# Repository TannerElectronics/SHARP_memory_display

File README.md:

# SHARP_memory_display
SPI breakout board example code for the Arduino platform

This example sketch is based on and requires two libraries from Adafruit. 

You will need to have installed the Adafruit GFX library from 
https://github.com/adafruit/Adafruit-GFX-Library 

As well as her SHARP library from 
https://github.com/adafruit/Adafruit_SHARP_Memory_Display

Images of front and back of module.

Click image below to follow link to YouTube demo.

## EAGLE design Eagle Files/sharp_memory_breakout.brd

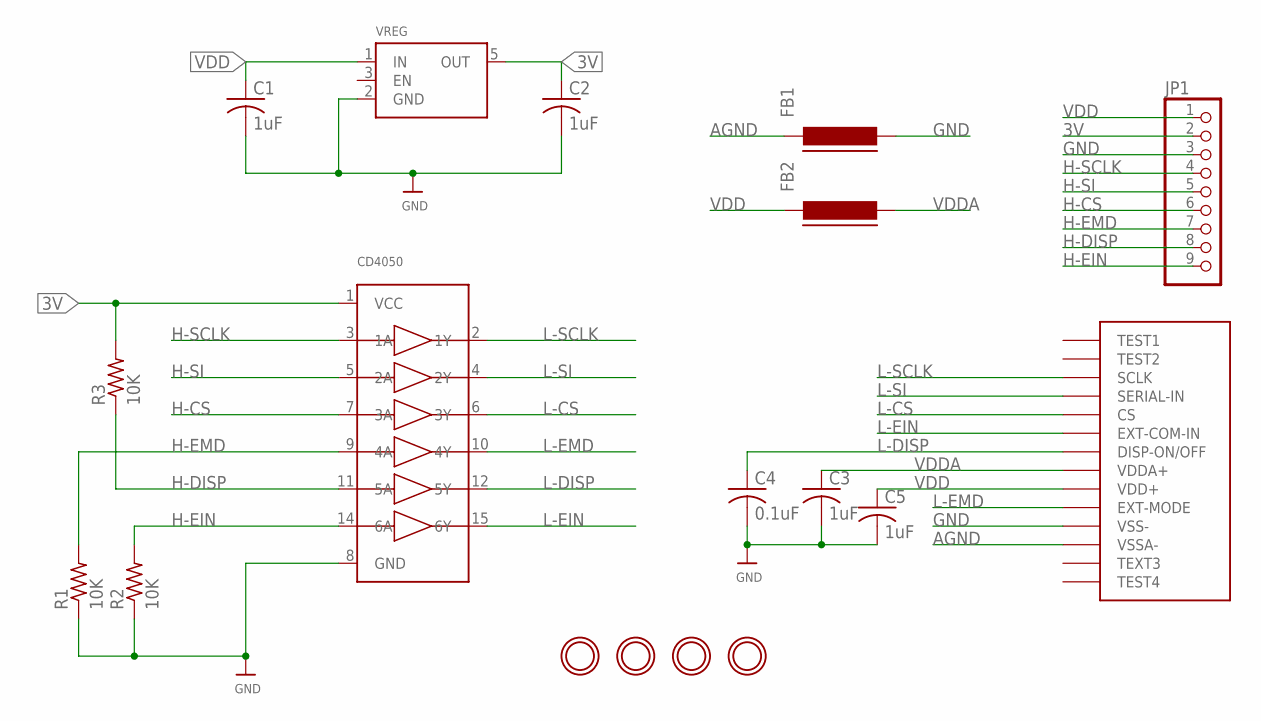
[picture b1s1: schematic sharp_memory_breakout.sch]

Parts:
C1, C2, C3, C5: 1uF; C0805K
C4: 0.1uF; C0805K
CD4050: 74HC4050D; SOIC16
FB1, FB2: FERRITE-0603; FB603
JP1: PINHD-1X9; 1X09-BIG
R1, R2, R3: 10K; R0805
U$1: SHARP-MEMORY
U$2, U$3, U$4, U$5: MOUNTINGHOLE3.0THIN; MOUNTINGHOLE_3.0_PLATEDTHIN
VREG: ADP121; SOT23-5

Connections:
3V: C2.1, CD4050.1 (VCC), JP1.2, R3.2, VREG.5 (OUT)
AGND: FB1.1, U$1.P$12 (VSSA-)
GND: C1.2, C2.2, C3.2, C4.2, C5.2, CD4050.8 (GND), FB1.2, JP1.3, R1.1, R2.1, U$1.P$11 (VSS-), VREG.2 (GND)
H-CS: CD4050.7 (3A), JP1.6
H-DISP: CD4050.11 (5A), JP1.8, R3.1
H-EIN: CD4050.14 (6A), JP1.9, R2.2
H-EMD: CD4050.9 (4A), JP1.7, R1.2
H-SCLK: CD4050.3 (1A), JP1.4
H-SI: CD4050.5 (2A), JP1.5
L-CS: CD4050.6 (3Y), U$1.P$5 (CS)
L-DISP: C4.1, CD4050.12 (5Y), U$1.P$7 (DISP-ON/OFF)
L-EIN: CD4050.15 (6Y), U$1.P$6 (EXT-COM-IN)
L-EMD: CD4050.10 (4Y), U$1.P$10 (EXT-MODE)
L-SCLK: CD4050.2 (1Y), U$1.P$3 (SCLK)
L-SI: CD4050.4 (2Y), U$1.P$4 (SERIAL-IN)
VDD: C1.1, C5.1, FB2.1, JP1.1, U$1.P$9 (VDD+), VREG.1 (IN)
VDDA: C3.1, FB2.2, U$1.P$8 (VDDA+)

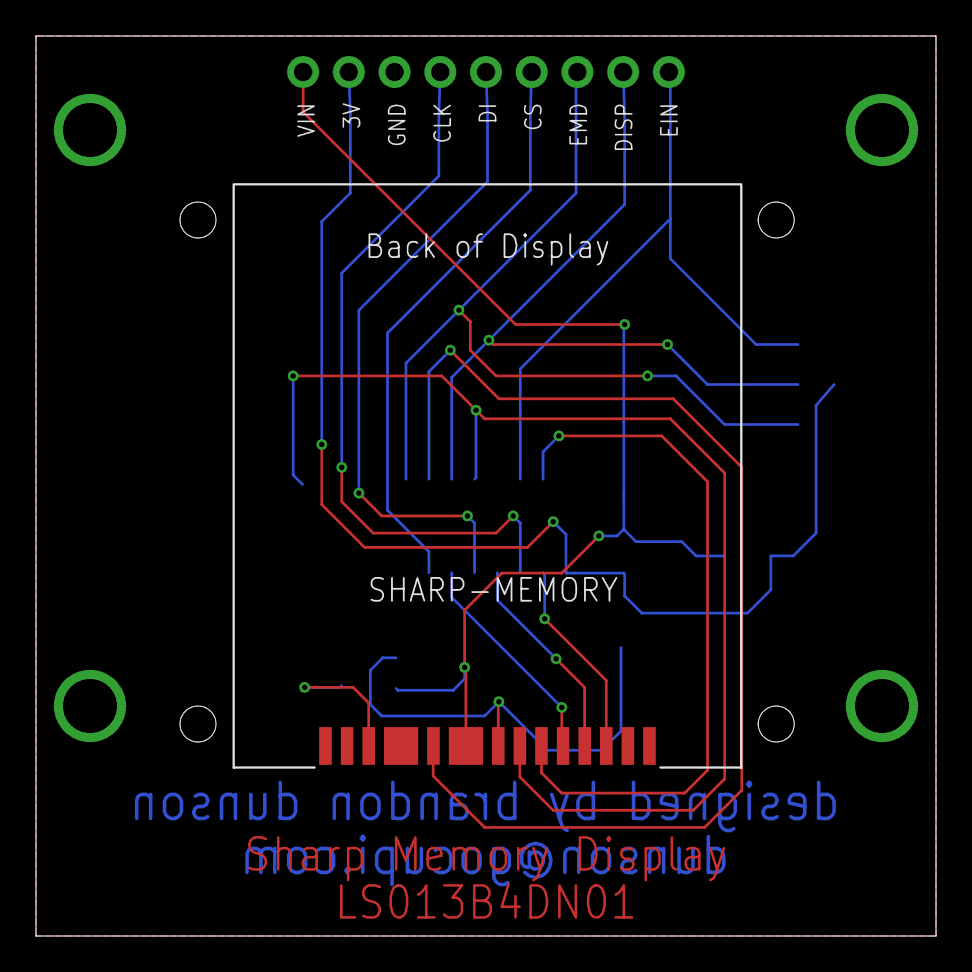
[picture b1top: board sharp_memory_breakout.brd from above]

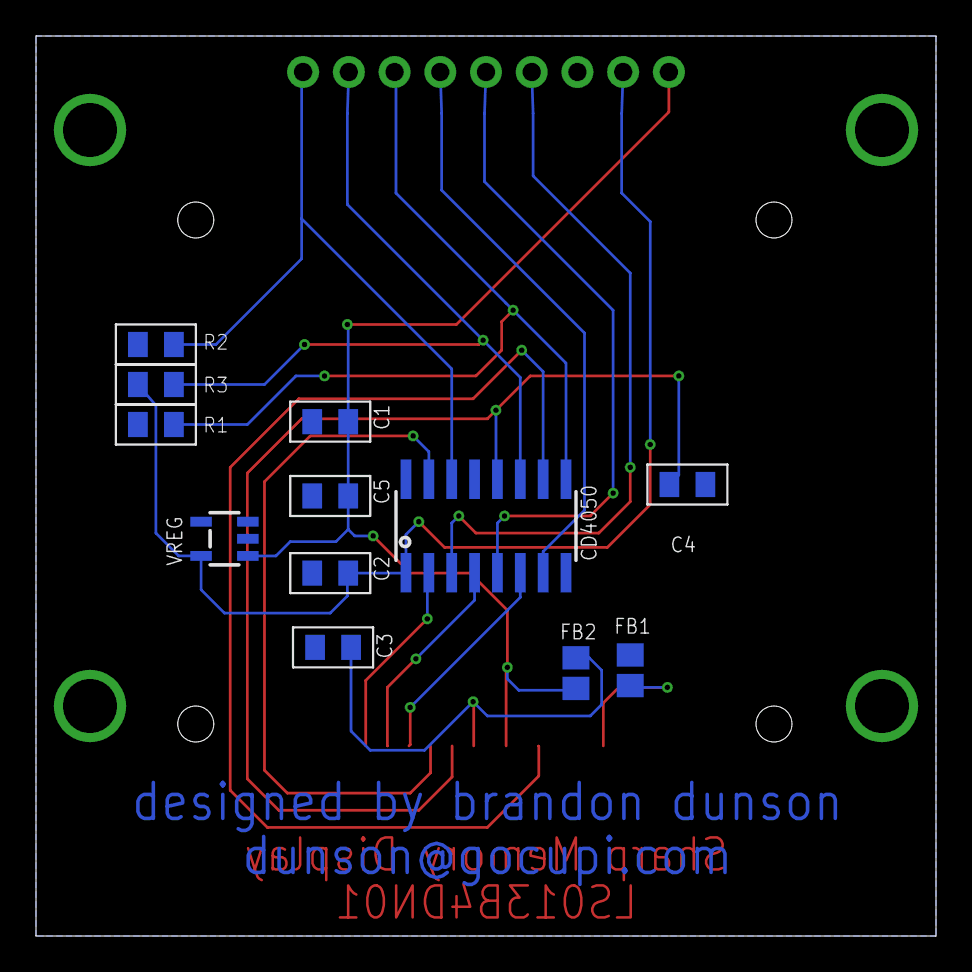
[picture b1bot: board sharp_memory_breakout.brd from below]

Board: 2 copper layers, 50.0 x 50.0 mm, 18 parts (12 on the bottom side), 17 nets.

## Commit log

2016-05-29 add images and video to readme
2016-05-29 Added design files
    Included Eagle schematic, board, gerbers, and a PDF of the schematic.

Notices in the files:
parts and their libraries:
TL2575: This work is placed in the public domain, and may be freely used for commercial and non-commercial work with the following conditions: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
